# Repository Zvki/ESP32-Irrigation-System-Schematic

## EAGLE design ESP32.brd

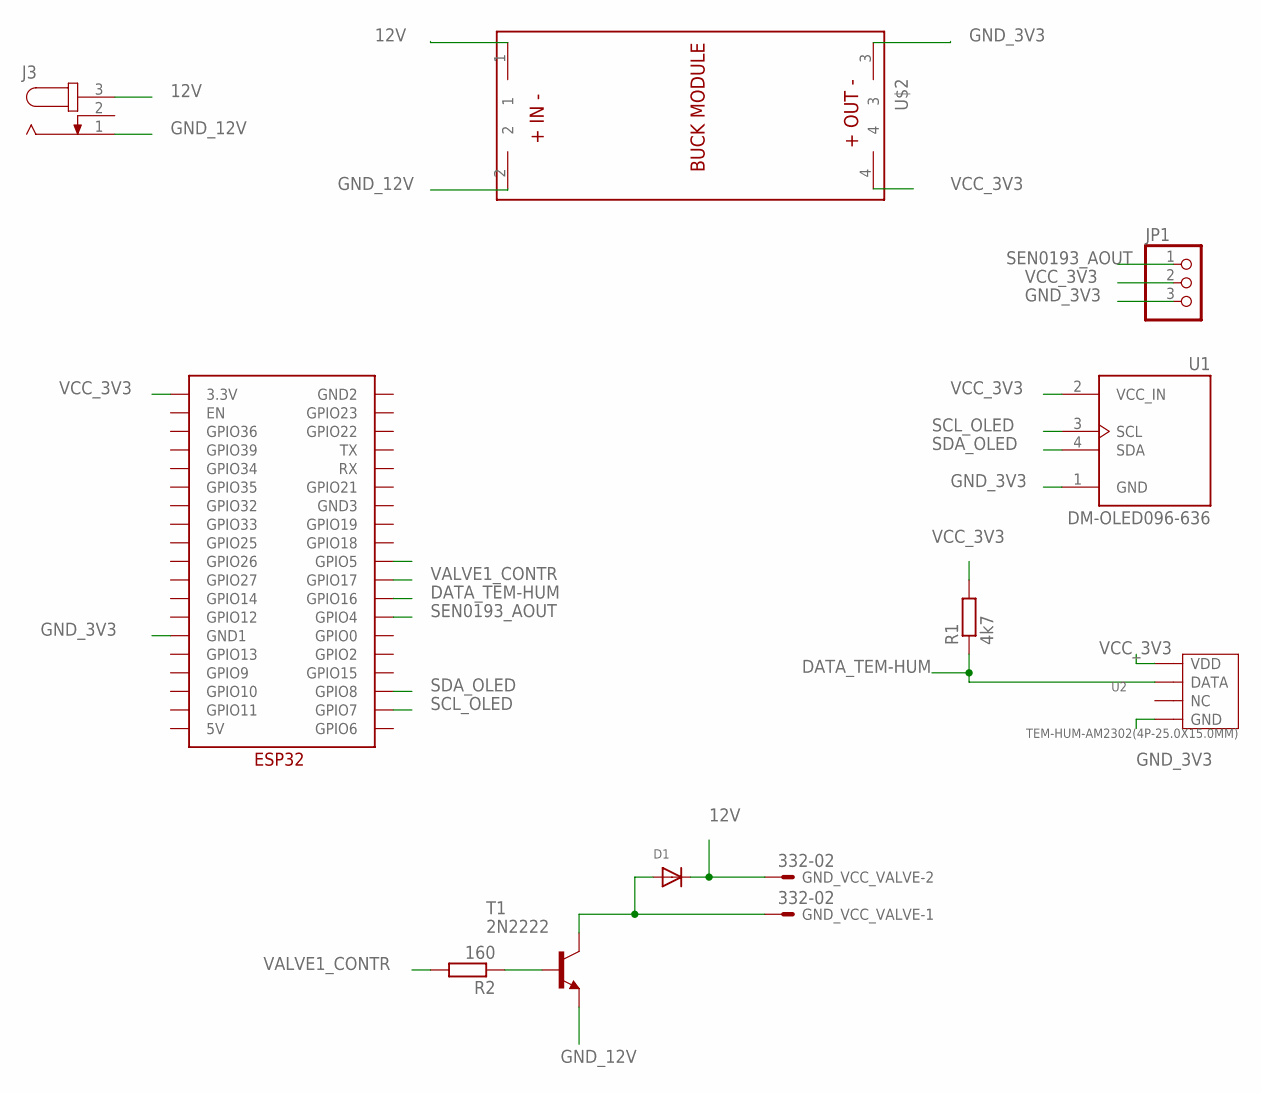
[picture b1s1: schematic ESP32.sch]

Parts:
D1: DIODESOD-123; SOD-123
GND_VCC_VALVE: 332-02
J3: JACK-PLUG1; SPC4078
JP1: PINHD-1X3; 1X03
R1: 4k7; 0204/5
R2: 160; 0204/5
T1: 2N2222; TO92-EBC-OVAL
U1: DM-OLED096-636; MODULE_DM-OLED096-636
U2: TEM-HUM-AM2302(4P-25.0X15.0MM); SNR4-2.54-25.0X15.0X7.0MM
U$1: ESP32_GRBL
U$2: BUCK_MODULEWITH_SMDPADS&THROUGHHOLES; BUCK_MODULE

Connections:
12V: D1.C, GND_VCC_VALVE.2, J3.3, U$2.1
DATA_TEM-HUM: R1.1, U2.P$2 (DATA), U$1.GPIO16
GND_3V3: JP1.3, U1.1 (GND), U2.P$4 (GND), U$1.GND1, U$2.3
GND_12V: J3.1, T1.E, U$2.2
unnamed: R2.1, T1.B
unnamed: D1.A, GND_VCC_VALVE.1, T1.C
SCL_OLED: U1.3 (SCL), U$1.GPIO5, U$1.GPIO7
SDA_OLED: U1.4 (SDA), U$1.GPIO8
SEN0193_AOUT: JP1.1, U$1.GPIO4
VALVE1_CONTR: R2.2, U$1.GPIO17
VCC_3V3: JP1.2, R1.2, U1.2 (VCC_IN), U2.P$1 (VDD), U$1.3.3V, U$2.4

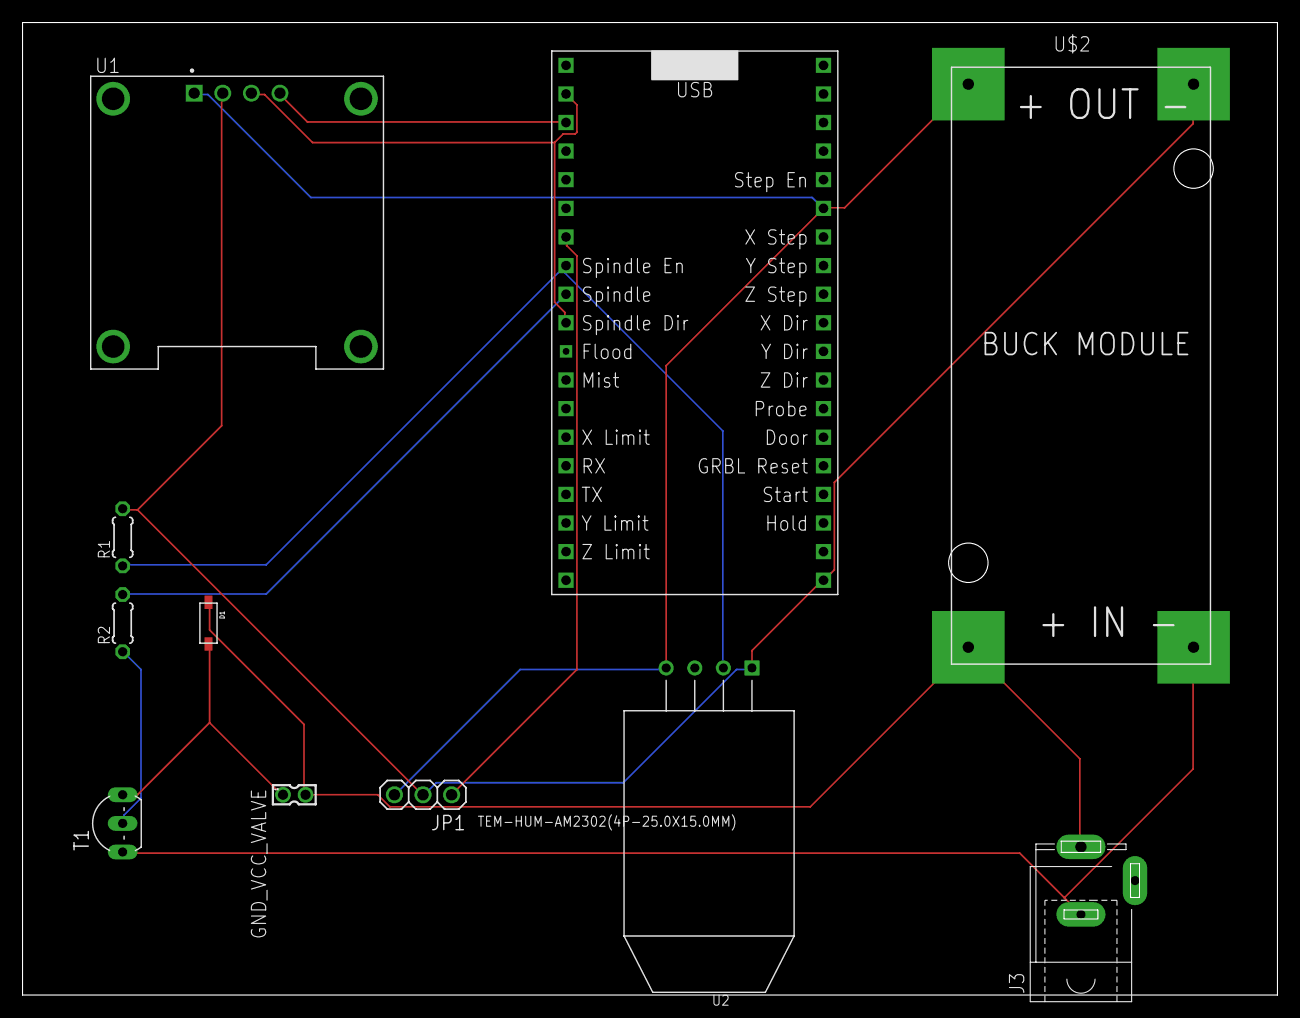
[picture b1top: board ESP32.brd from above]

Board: 2 copper layers, 111.4 x 86.3 mm, 11 parts (0 on the bottom side), 11 nets.

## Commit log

2024-11-20 update_pcb
2024-11-26 Bash test 1
2025-01-05 feat; changed pin connections and resistor ohm value, also made new board project
2025-01-08 docs: added pttx
2025-01-22 feat: changed resistancy of transistor base resistor
